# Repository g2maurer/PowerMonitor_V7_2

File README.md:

# PowerMonitor_V7_2

## Code:
* ESP32 code files.
* Compile with Arduino Sketch IDE version 1.8.19.
* ESP Board Manager - esp32 by Espressif Systems version 2.0.17.
	* NOTE: Don't try to use newer versions (3.0.x or newer).
* Board: DOIT ESP32 DEVKIT V1

* Required Libraries:
	* RV3028C7.h - Realtime Clock
	* TimeLib.h -
	* Adafruit_ADS1X15.h - Analog-to-Digital converter.
	* WiFi.h
	* WiFiUdp.h
	* NTPClient.h
	* TFT_eSPI.h - TFT screen with Touch.
	* SD.h - SD memory card.
	* SPIFFS.h

## Enclosure:
* STL files for enclosure (front and back).
* FreeCAD enclosure design files.

## Images:
* Image files for PCB and enclosure.

## PCB:
* KiCAD
	* PCB design files.
* PCB Components:
	* ESP32-WROOM-32S.
	* 3.5 inch TFT with Touch. 
		* SPI interface.
	* ADS1015 Analog to Digital converter ICs. 
		* Configured in differntail mode, two CT channels per A2D converter IC.
	* CH340K USB to serial inteface IC.
		* microUSB interface (USB-B).
	* RV3028__C7 Realtime Clock IC and battery. 
		* Not required if WiFi connected to get the time via NTP.

## Misc:
* TFT user setup file. 
	* Contains the ESP32 to TFT pin definitions.
	* The TFT_eSPI "User_Setup_Select.h" file selects the User_Setup file. 
	* Use ILI9488_g2m.h file found in Misc directory for User_Setup file.

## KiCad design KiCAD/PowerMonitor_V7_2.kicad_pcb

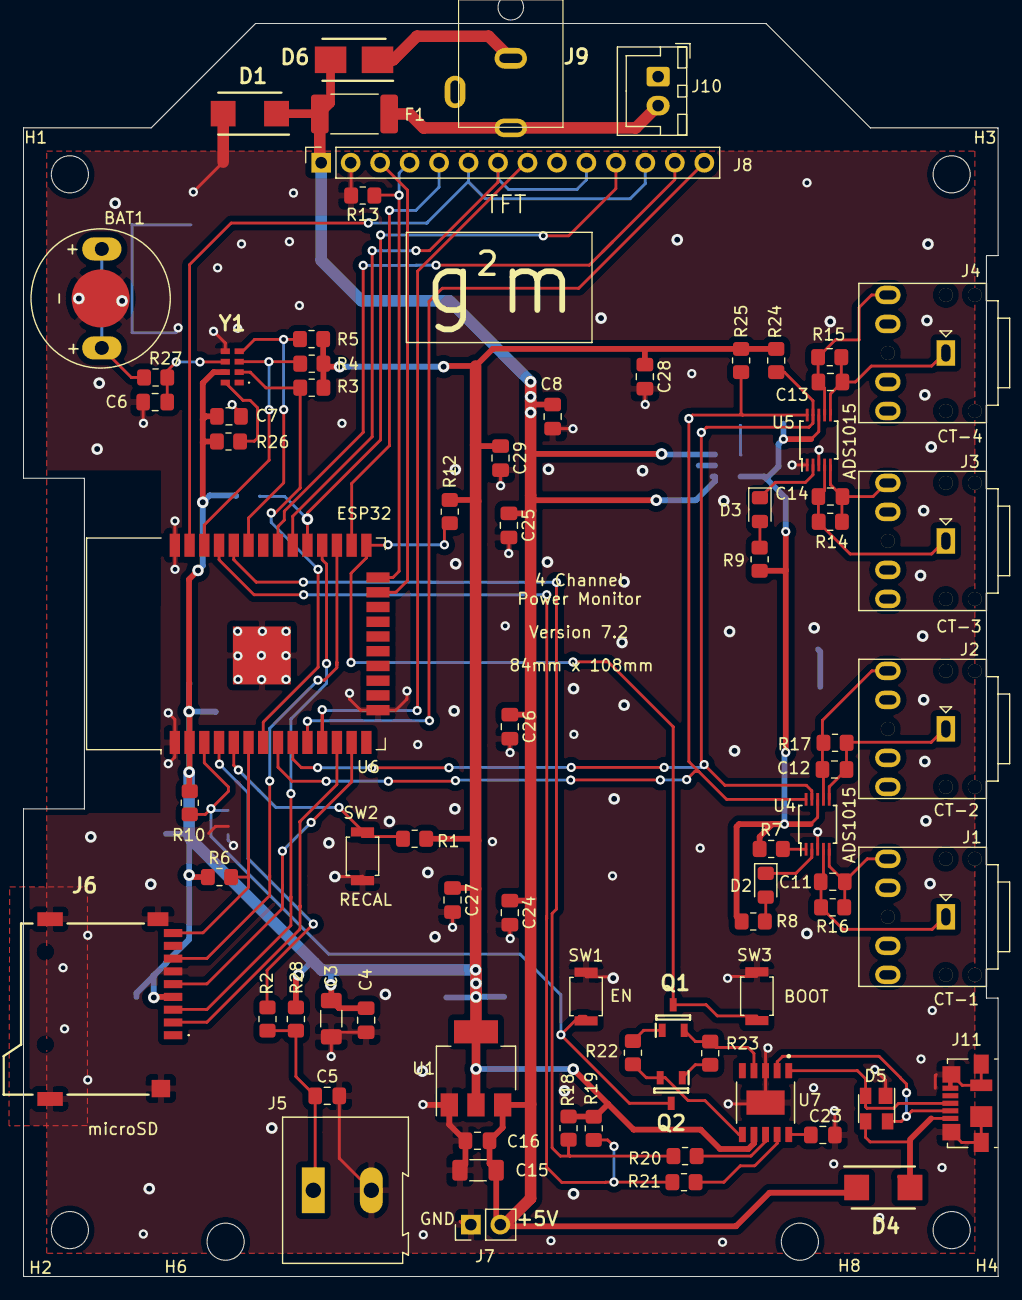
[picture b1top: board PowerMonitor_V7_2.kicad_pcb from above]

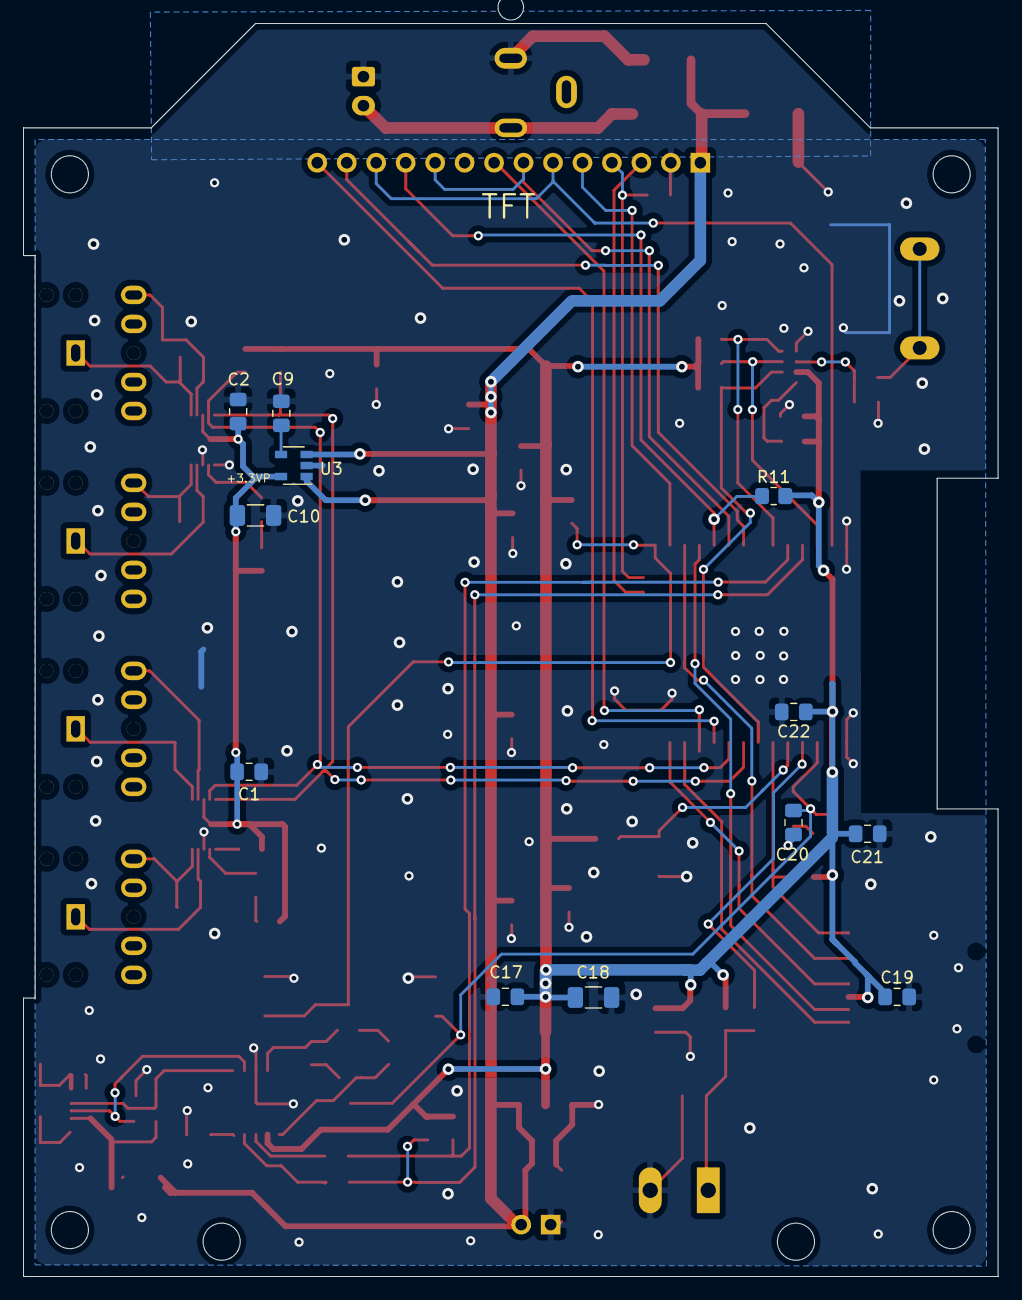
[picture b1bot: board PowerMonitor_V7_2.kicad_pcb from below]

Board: 2 copper layers, 84.0 x 108.0 mm, 94 parts (12 on the bottom side), 58 nets.

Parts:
BAT1: SR754; Battery_Retainer_size_13
C1, C2, C4, C5, C6, C7, C16, C17, C19, C21, C22, C23, C24, C25, C26, C27, C28, C29: 100nF; C_0805_2012Metric_Pad1.18x1.45mm_HandSolder
C3, C15, C18: 10uF; C_1206_3216Metric_Pad1.33x1.80mm_HandSolder
C8: 1uF; C_0805_2012Metric_Pad1.18x1.45mm_HandSolder
C9, C11, C12, C13, C14, C20: 10nF; C_0805_2012Metric_Pad1.18x1.45mm_HandSolder
C10: 2.2uF; C_1206_3216Metric_Pad1.33x1.80mm_HandSolder
D1: 1N5819; DIOM5436X295N
D2, D3: LED; LED_0805_2012Metric_Pad1.15x1.40mm_HandSolder
D4: 5819SMJE3_TR13; DIOM5436X295N
D5: SP0503BAHT; SOT-143
D6: SMAZ6V2; DO-214AA
F1: Polyfuse_Small; Fuse_2512_6332Metric_Pad1.52x3.35mm_HandSolder
H1, H2, H3, H4: MountingHole; MountingHole_3.2mm_M3
H6, H8: TFTHole; MountingHole_3.2mm_M3
J1: CT-1; Jack_3.5mm_PJ307_Horizontal
J2: CT-2; Jack_3.5mm_PJ307_Horizontal
J3: CT-3; Jack_3.5mm_PJ307_Horizontal
J4: CT-4; Jack_3.5mm_PJ307_Horizontal
J5: Thermister; TerminalBlock_Altech_AK300-2_P5.00mm
J6: MSD-4-A; MSD4A
J7: Test_5V; PinHeader_1x02_P2.54mm_Vertical
J8: TFT; PinSocket_1x14_P2.54mm_Vertical
J9: Barrel_Jack_Switch; PJ-059A
J10: +5V IN; JST_XH_B2B-XH-A_1x02_P2.50mm_Vertical
J11: USB_B_Micro; USB_Micro-B_Molex_47346-0001
Q1, Q2: MMSS8050-H-TP; SOT95P237X125-3N
R1, R3, R6, R7, R8, R9, R11, R12, R13, R14, R15, R16, R17, R18, R19, R24, R25, R26: 10k; R_0805_2012Metric_Pad1.20x1.40mm_HandSolder
R2: 1k; R_0805_2012Metric_Pad1.20x1.40mm_HandSolder
R4, R5: 4.7k; R_0805_2012Metric_Pad1.20x1.40mm_HandSolder
R10: 12k; R_0805_2012Metric_Pad1.20x1.40mm_HandSolder
R20, R21, R27: 470; R_0805_2012Metric_Pad1.20x1.40mm_HandSolder
R22, R23: 5.1k; R_0805_2012Metric_Pad1.20x1.40mm_HandSolder
R28: 1.5k; R_0805_2012Metric_Pad1.20x1.40mm_HandSolder
SW1: EN; SW_SPST_ALPS_SKRKA
SW2: Recal Touch; SW_SPST_ALPS_SKRKA
SW3: Boot; SW_SPST_ALPS_SKRKA
U1: AMS1117-3.3; SOT-223-3_TabPin2
U3: LP2985-3.3; SOT-23-5
U4, U5: ADS1015IDGS; TSSOP-10_3x3mm_P0.5mm
U6: ESP32-WROOM; ESP32-WROOM-32
U7: CH340K; SOP100P600X160-11N
Y1: RV-3028-C7_32.768KHZ_1PPM-TA-QA; RV3028C732768KHZ1PPMTAQA

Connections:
+3.3VP: C1.1, C2.2, C10.1, R7.1, R8.1, R9.1, U3.5, U4.8, U5.8
+3V3: C3.1, C4.1, C7.1, C17.1, C18.1, C19.1, C21.1, C22.1, C27.1, C28.1, C29.1, J6.4, R1.1, R3.1, R4.1, R5.1, R6.1, R10.1, R11.2, R12.1, R18.1, R19.1, R24.1, R25.1, R26.1, R28.1, U1.2, U6.2, U7.7, Y1.7
+5V: C8.1, C15.1, C16.1, C24.1, C25.1, C26.1, D1.1, D4.1, D6.2, F1.2, J7.2, J8.1, U1.3, U3.1, U3.3
/MISO: J8.13, U6.31
/MOSI: J8.6, J8.12, U6.37
/SCK: J8.7, J8.10, U6.30
/TFT_CS: J8.3, U6.23
/TFT_DC: J8.5, U6.26
/TFT_RESET: J8.4, R13.1, U6.24
/Touch_CS: J8.11, R11.1, U6.29
ADC1_0: C5.1, J5.1, R2.2, R28.2
BOOT: Q1.3, R12.2, SW3.1, U6.25
GND: BAT1.1, C1.2, C2.1, C3.2, C4.2, C5.2, C6.2, C7.2, C8.2, C9.2, C10.2, C15.2, C16.2, C17.2, C18.2, C19.2, C20.2, C21.2, C22.2, C23.1, C24.2, C25.2, C26.2, C27.2, C28.2, C29.2, D1.2, D5.1, D6.1, J5.2, J6.6, J6.G1, J6.G2, J6.G3, J6.G4, J7.1, J8.2, J9.2, J10.1, J11.5, J11.6, R13.2, SW1.1, SW2.1, SW3.2, U1.1, U3.2, U4.3, U5.1, U5.3, U6.1, U6.15, U6.38, U6.39, U7.3, U7.11, Y1.5
unnamed: C6.1, R27.2, Y1.6
unnamed: C9.1, U3.4
unnamed: C11.1, J1.5, R16.1, U4.5
unnamed: C11.2, J1.1, R16.2, U4.4
unnamed: C12.1, J2.5, R17.1, U4.7
unnamed: C12.2, J2.1, R17.2, U4.6
unnamed: C13.1, J4.5, R15.1, U5.7
unnamed: C13.2, J4.1, R15.2, U5.6
unnamed: C14.1, J3.5, R14.1, U5.5
unnamed: C14.2, J3.1, R14.2, U5.4
unnamed: C23.2, U7.10
unnamed: D2.1, U4.2
unnamed: D2.2, R8.2
unnamed: D3.1, U5.2
unnamed: D3.2, R9.2
unnamed: D4.2, D5.3, J11.1
unnamed: D5.2, J11.3, U7.1
unnamed: D5.4, J11.2, U7.2
unnamed: F1.1, J9.1, J10.2
unnamed: Q1.1, R22.1
unnamed: Q1.2, R23.2, U7.4
unnamed: Q2.1, R23.1
unnamed: Q2.2, R22.2, U7.6
unnamed: R1.2, SW2.2, U6.5
unnamed: R2.1, U6.4
unnamed: R7.2, U4.1
unnamed: R20.2, U7.8
unnamed: R21.2, U7.9
unnamed: R26.2, Y1.8
RST: C20.1, Q2.3, R10.2, SW1.2, U6.3
RTC_INT: R3.2, U6.7, Y1.2
RXD: R18.2, R20.1, U6.34
SCL_0: R4.2, U6.36, Y1.3
SCL_1: R25.2, U4.10, U5.10, U6.8
SDA_0: R5.2, U6.33, Y1.4
SDA_1: R24.2, U4.9, U5.9, U6.9
SD_CLK: J6.5, U6.13
SD_CS: J6.2, U6.12
SD_DET: J6.CD1, R6.2, U6.6
SD_MISO: J6.7, U6.27
SD_MOSI: J6.3, U6.28
TFT_LED: J8.8, U6.11
TXD: R19.2, R21.1, U6.35
TouchInt: J8.14, U6.10
VBackup: BAT1.2, R27.1

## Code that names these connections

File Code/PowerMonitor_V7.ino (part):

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// ----- TFT -----             Net Name
//#define TFT_DIN 23          // MOSI & Touch_DIN
//#define TFT_SCK 18          // SCK (both TFT and Touch)
#define TFT_LED   26          // TFT_LED, control pin
#define TFT_CS    15          // TFT_CS
#define TFT_RESET 2           // TFT_RESET
#define TFT_DC    4           // TFT_DC
//#define TOUCH_INT_PIN 25    // TouchInt
//#define TOUCH_DOUT  19      // Touch_DOUT & MISO
#define TOUCH_CS_PIN    5     // Touch_CS

// ----- ADC -----
#define ADC1_0  36      // (36=VP) Temperature Sensor

// ------ RTC -----
#define RTC_INT_PIN   35      // RTC_INT

//
// Wire definitions
//
#define SDA_0 21    // SDA_0
#define SCL_0 22    // SCL_0

#define SDA_1 33    // SDA_1
#define SCL_1 32    // SCL_1

TwoWire I2C_0 = TwoWire(0);     // RTC
TwoWire I2C_1 = TwoWire(1);     // ADC's
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//
//#ifdef SD_SUPPORT
// Pin Definitions          Net Name
#define HSPI_MISO   16    // SD_MISO
#define HSPI_MOSI   17    // SD_MOSI
#define HSPI_SCLK   14    // SD_CLK
#define HSPI_SS     27    // SD_CS
#define SD_CARD_DET 34    // SD_DET

#define SD_SPI_FREQ 1000000
SPIClass hspi = SPIClass(HSPI);
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  //
  // Setup TFT LED
  //
  pinMode(TFT_LED, OUTPUT);
  digitalWrite(TFT_LED, HIGH);
  
  touch_calibrate();
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
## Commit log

2024-11-03 Initial Release
2024-11-04 Update with images
2024-11-05 Renamed Images
2024-11-05 ReadMe update
